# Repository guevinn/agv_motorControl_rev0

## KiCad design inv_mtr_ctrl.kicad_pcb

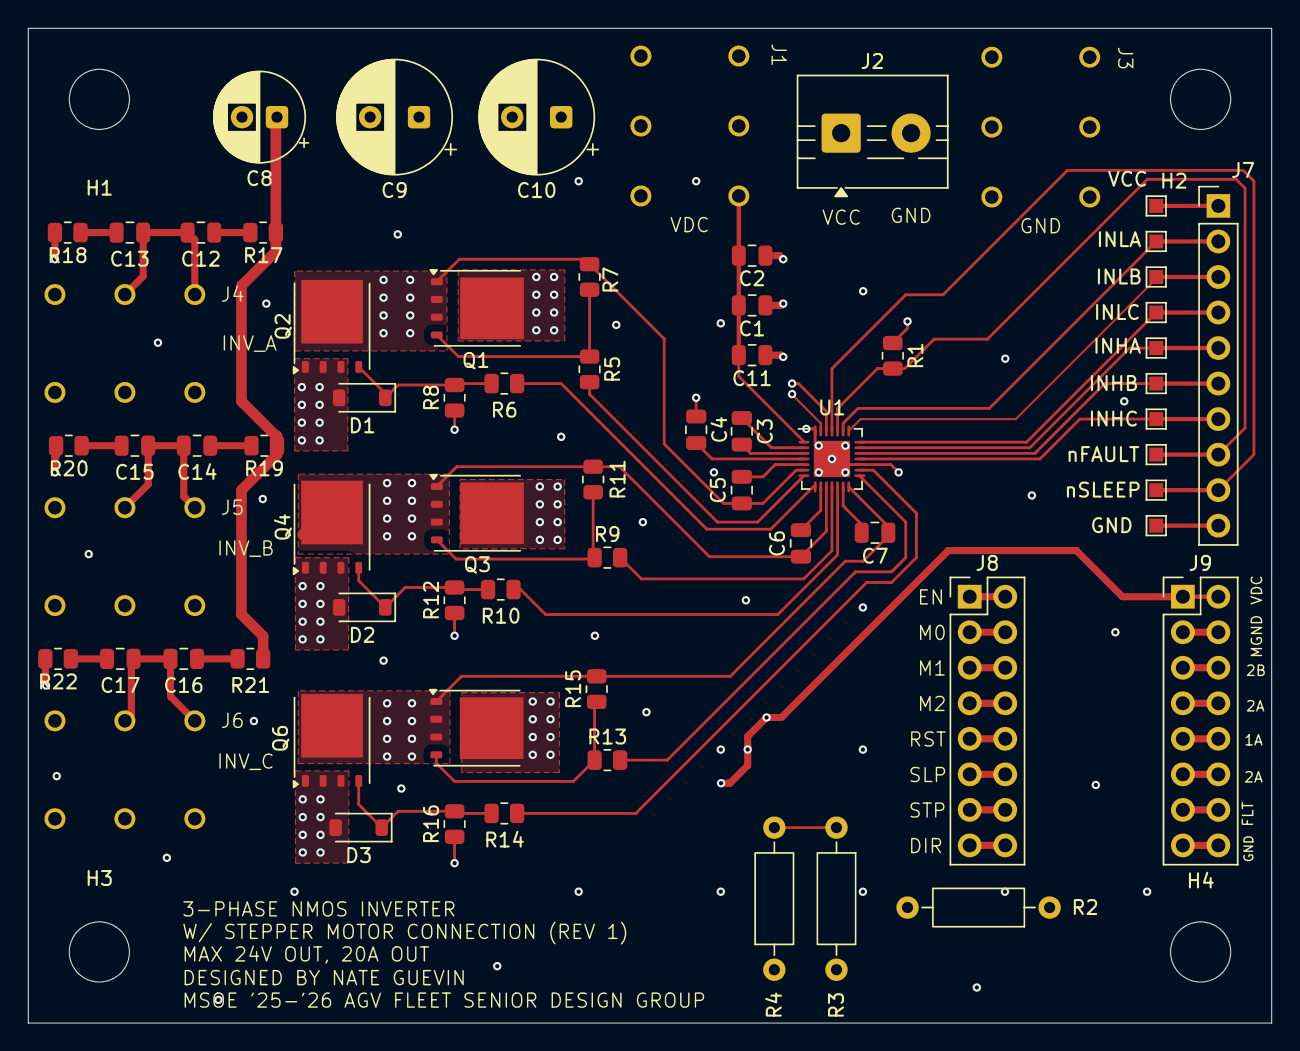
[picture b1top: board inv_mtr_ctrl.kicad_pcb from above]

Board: 4 copper layers, 88.9 x 71.1 mm, 72 parts (0 on the bottom side), 54 nets.

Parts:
C1, C4: 10u; C_0805_2012Metric
C2: .1u; C_0805_2012Metric
C3: .47u; C_0805_2012Metric
C5, C6, C7, C11: .01u; C_0805_2012Metric
C8: 100u; CP_Radial_D6.3mm_P2.50mm
C9, C10: 100u; CP_Radial_D8.0mm_P3.50mm
C12, C13, C14, C15, C16, C17: CSNUB; C_0805_2012Metric
D1, D2, D3: D_Zener; D_SOD-123
GND: TestPoint; TestPoint_Pad_1.0x1.0mm
H1, H2, H3, H4: M4; MountingHole_4.3mm_M4
INHA: TestPoint; TestPoint_Pad_1.0x1.0mm
INHB: TestPoint; TestPoint_Pad_1.0x1.0mm
INHC: TestPoint; TestPoint_Pad_1.0x1.0mm
INLB: TestPoint; TestPoint_Pad_1.0x1.0mm
INLC: TestPoint; TestPoint_Pad_1.0x1.0mm
J1, J3, J4, J5, J6: 7799; M4 30A
J2: Screw_Terminal_01x02; TerminalBlock_MaiXu_MX126-5.0-02P_1x02_P5.00mm
J7: Conn_01x10; PinHeader_1x10_P2.54mm_Vertical
J8, J9: Conn_02x08_Odd_Even; PinHeader_2x08_P2.54mm_Vertical
Q1, Q2, Q3, Q4, Q5, Q6: BSC067N06LS3GATMA1; TDSON-8-1
R1, R7, R8, R11, R12, R15, R16: 10k; R_0805_2012Metric
R2: 1k; R_Axial_DIN0207_L6.3mm_D2.5mm_P10.16mm_Horizontal
R3: 141k; R_Axial_DIN0207_L6.3mm_D2.5mm_P10.16mm_Horizontal
R4: 10k; R_Axial_DIN0207_L6.3mm_D2.5mm_P10.16mm_Horizontal
R5, R6, R9, R10, R13, R14: 31; R_0805_2012Metric
R17, R18, R19, R20, R21, R22: RSNUB; R_0805_2012Metric
TP8: TestPoint; TestPoint_Pad_1.0x1.0mm
U1: DRV8328_4mm_x_4mm_WQFN
VCC: TestPoint; TestPoint_Pad_1.0x1.0mm
nFAULT: TestPoint; TestPoint_Pad_1.0x1.0mm
nSLEEP: TestPoint; TestPoint_Pad_1.0x1.0mm

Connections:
/1A: J9.9, J9.10
/1B: J9.7, J9.8
/2A: J9.11, J9.12
/2B: J9.5, J9.6
/A_INV: C5.1, C12.1, C13.2, J4.1, Q1.1 (S), Q1.2 (S), Q1.3 (S), Q2.5 (D), R7.2, U1.6 (SHA)
/B_INV: C6.1, C14.1, C15.2, J5.1, Q3.1 (S), Q3.2 (S), Q3.3 (S), Q4.5 (D), R11.2, U1.10 (SHB)
/C_INV: C7.1, C16.1, C17.2, J6.1, Q5.1 (S), Q5.2 (S), Q5.3 (S), Q6.5 (D), R15.2, U1.14 (SHC)
/DIR: J8.15, J8.16
/EN_DRV25: J8.1, J8.2
/FAULT: J9.13, J9.14
/GHA: R5.2, U1.7 (GHA)
/GHB: R9.2, U1.11 (GHB)
/GHC: R13.2, U1.15 (GHC)
/GLA: R6.2, U1.8 (GLA)
/GLB: R10.2, U1.12 (GLB)
/GLC: R14.2, U1.16 (GLC)
/GVDD: C4.2, U1.4 (GVDD)
/INHA: INHA.1, J7.5, U1.20 (INHA)
/INHB: INHB.1, J7.6, U1.19 (INHB)
/INHC: INHC.1, J7.7, U1.18 (INHC)
/INLA: J7.2, TP8.1, U1.23 (INLA)
/INLB: INLB.1, J7.3, U1.22 (INLB)
/INLC: INLC.1, J7.4, U1.21 (INLC)
/M0: J8.3, J8.4
/M1: J8.5, J8.6
/M2: J8.7, J8.8
/M_GND: J9.3, J9.4
/RST: J8.9, J8.10
/SLP: J8.11, J8.12
/STEP: J8.13, J8.14
/nFAULT: J7.8, R1.2, U1.24 (nFAULT), nFAULT.1
/nSLEEP: J7.9, U1.25 (nSLEEP), nSLEEP.1
GND: C1.1, C2.1, C4.1, C8.2, C9.2, C10.2, C11.1, D1.2 (A), D2.2 (A), D3.2 (A), GND.1, J2.2, J3.1, J7.10, J9.15, J9.16, Q2.1 (S), Q2.2 (S), Q2.3 (S), Q4.1 (S), Q4.2 (S), Q4.3 (S), Q6.1 (S), Q6.2 (S), Q6.3 (S), R2.1, R4.1, R8.1, R12.1, R16.1, R18.2, R20.2, R22.2, U1.17 (LSS), U1.28 (GND), U1.29 (THERM)
unnamed: C12.2, R17.2
unnamed: C13.1, R18.1
unnamed: C14.2, R19.2
unnamed: C15.1, R20.1
unnamed: C16.2, R21.2
unnamed: C17.1, R22.1
unnamed: D1.1 (K), Q2.4 (G), R6.1, R8.2
unnamed: D2.1 (K), Q4.4 (G), R10.1, R12.2
unnamed: D3.1 (K), Q6.4 (G), R14.1, R16.2
unnamed: Q1.4 (G), R5.1, R7.1
unnamed: Q3.4 (G), R9.1, R11.1
unnamed: Q5.4 (G), R13.1, R15.1
unnamed: C5.2, U1.5 (BSTA)
unnamed: C6.2, U1.9 (BSTB)
unnamed: C7.2, U1.13 (BSTC)
unnamed: C3.2, U1.3 (CPH)
unnamed: C3.1, U1.2 (CPL)
unnamed: R2.2, U1.27 (DT)
unnamed: R3.1, R4.2, U1.26 (VDSLVL)
VCC: J2.1, J7.1, R1.1, R3.2, VCC.1
VDC: C1.2, C2.2, C8.1, C9.1, C10.1, C11.2, J1.1, J9.1, J9.2, Q1.5 (D), Q3.5 (D), Q5.5 (D), R17.1, R19.1, R21.1, U1.1 (PVDD)

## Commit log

2025-11-04 Updated stackup
2025-11-04 Component placements
2025-11-04 Placed test points and decoupling caps
2025-11-04 routed passives and test points
2025-11-04 Routed non-inverter signals and moved header signals around
2025-11-05 Ground pours on layers 2 and 3
2025-11-05 Drew pour areas prior to getting advice from Dr. Rothe
2025-11-06 Updated pour areas to have larger area for escape traces on FET to phase connections. Trace length of GL traces was compromised to do this
2025-11-06 Moved screw terminals
2025-11-06 Checkpoint before filling zones
2025-11-06 Initial zone fill and connections
2025-11-07 Updated fill areas to be solid instead of thermal
2025-11-07 Pre-Rothe meeting board
2025-11-07 Added additional copper pours and moved through hole resistors
2025-11-07 Updated trace routing and boostrap capacitor placement
2025-11-10 Starting point for Rothe meeting
2025-11-10 Alternative FET and trace layout prior to Rothe meeting
2025-11-10 Rothe review done. Implementing alternative inverter layout and then merging with origin
2025-11-10 Implemented alternative inverter routing and added splash on silkscreen
2025-11-11 Save point
2025-11-11 Placed ground plane stitching vias. Also switched all vias to through to minimize board cost
2025-11-14 Board layout initial BOM w/ layout
2025-11-18 Ordering PCB
